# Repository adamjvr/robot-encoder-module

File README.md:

# robot-encoder-module
LSI encoder chip carrier board for Archim motion control board can be used with any other controller

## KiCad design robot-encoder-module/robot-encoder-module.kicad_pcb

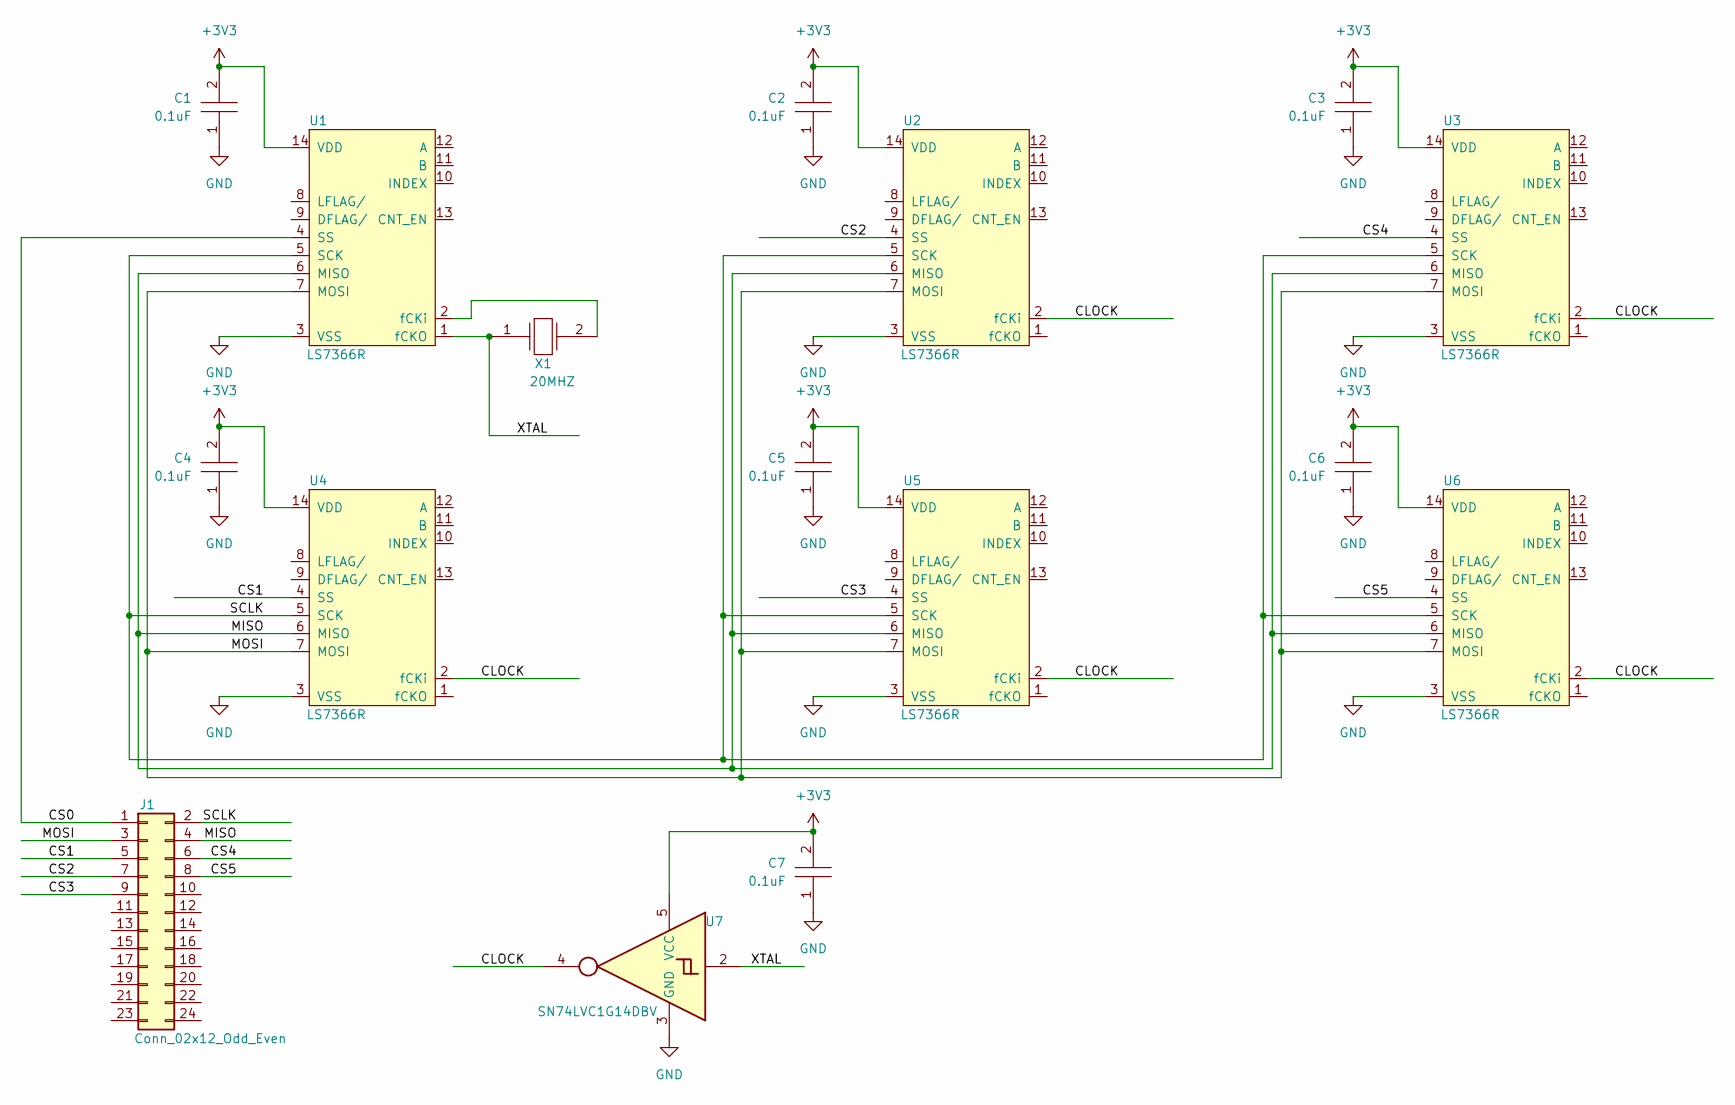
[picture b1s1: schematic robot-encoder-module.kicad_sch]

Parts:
C1, C2, C3, C4, C5, C6, C7: C0805C104M5RACTU; C0805; Tolerance 20%; Voltage 50V; MFR# C0805C104M5RACTU
J1: Conn_02x12_Odd_Even; PinHeader_2x12_P2.54mm_Vertical
U1, U2, U3, U4, U5, U6: LS7366R; DIP762W45P254L1917H533Q14; Tolerance N/A; Voltage 3-5.5V; MFR# LS7366R
U7: SN74LVC1G14DBV; SOT-23-5
X1: ABLS-20.000MHZ-B2-T; XTAL_ABLS-20.000MHZ-B2-T; Tolerance N/A; Voltage N/A; MFR# ABLS-20.000MHZ-B2-T

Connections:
+3V3: C1.2, C2.2, C3.2, C4.2, C5.2, C6.2, C7.2, U1.14 (VDD), U2.14 (VDD), U3.14 (VDD), U4.14 (VDD), U5.14 (VDD), U6.14 (VDD), U7.5 (VCC)
/CLOCK: U2.2 (fCKi), U3.2 (fCKi), U4.2 (fCKi), U5.2 (fCKi), U6.2 (fCKi), U7.4
/CS0: J1.1, U1.4 (SS)
/CS1: J1.5, U4.4 (SS)
/CS2: J1.7, U2.4 (SS)
/CS3: J1.9, U5.4 (SS)
/CS4: J1.6, U3.4 (SS)
/CS5: J1.8, U6.4 (SS)
/MISO: J1.4, U1.6 (MISO), U2.6 (MISO), U3.6 (MISO), U4.6 (MISO), U5.6 (MISO), U6.6 (MISO)
/MOSI: J1.3, U1.7 (MOSI), U2.7 (MOSI), U3.7 (MOSI), U4.7 (MOSI), U5.7 (MOSI), U6.7 (MOSI)
/SCLK: J1.2, U1.5 (SCK), U2.5 (SCK), U3.5 (SCK), U4.5 (SCK), U5.5 (SCK), U6.5 (SCK)
/XTAL: U1.1 (fCKO), U7.2, X1.1
GND: C1.1, C2.1, C3.1, C4.1, C5.1, C6.1, C7.1, U1.3 (VSS), U2.3 (VSS), U3.3 (VSS), U4.3 (VSS), U5.3 (VSS), U6.3 (VSS), U7.3 (GND)
unnamed: U1.2 (fCKi), X1.2

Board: 2 copper layers, 16 parts (0 on the bottom side), 14 nets, no tracks yet.

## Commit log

2023-12-24 KiCAD Project and Datasheets
    Datasheet for LS7366R chip and KiCAD project setup
2023-12-25 Basic Schematic
    Started basic schematic
2025-03-11 Schematic Tweaks and Board stackup
    Tweaks to scheamtic and creation of board stackup.
